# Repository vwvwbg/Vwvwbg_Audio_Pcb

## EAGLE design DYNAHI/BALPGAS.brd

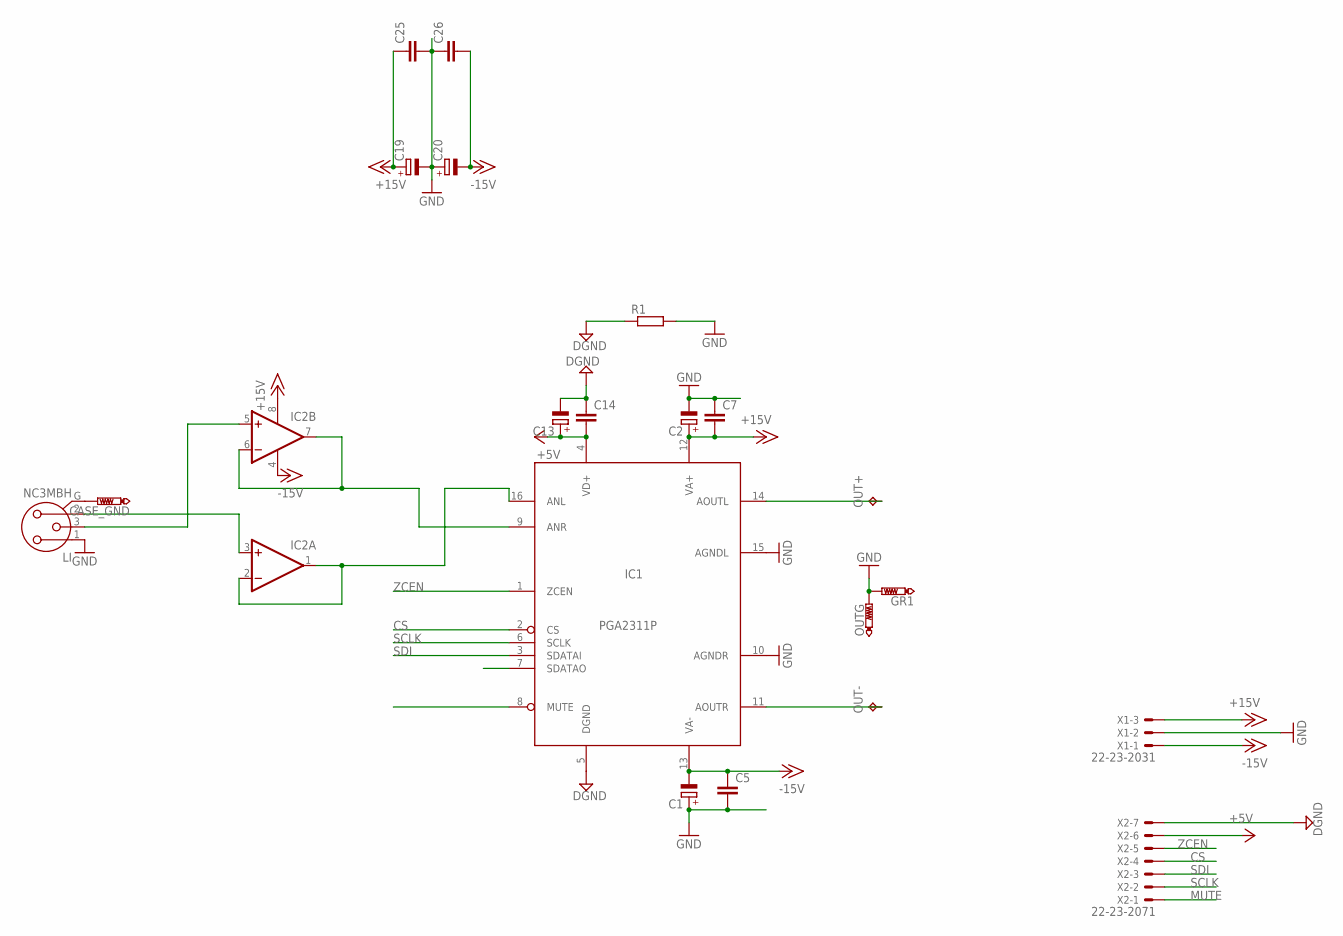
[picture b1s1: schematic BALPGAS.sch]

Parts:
C1, C2, C19, C20: CPOL-EUE5-10.5; E5-10,5
C5, C7, C25, C26: C-EU050-045X075; C050-045X075
C13: CPOL-EUSMCD; SMC_D
C14: C-EUC1206; C1206
CASE_GND: PTR1PAD1-17; P1-17
GR1: PTR1PAD1-17; P1-17
IC1: PGA2311P; DIL16
IC2: 2AMP_P8+4N; DIL08
LI: NC3MBH
OUT+: TPPAD1-20; P1-20
OUT-: TPPAD1-20; P1-20
OUTG: PTR1PAD1-17; P1-17
R1: R-EU_0207/10; 0207/10
X1: 22-23-2031
X2: 22-23-2071

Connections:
+5V: C13.+, C14.2, IC1.4 (VD+), X2.6
+15V: C2.+, C7.2, C19.+, C25.1, IC1.12 (VA+), IC2.8 (V+), X1.3
-15V: C1.-, C5.1, C20.-, C26.2, IC1.13 (VA-), IC2.4 (V-), X1.1
CS: IC1.2 (CS), X2.4
DGND: C13.-, C14.1, IC1.5 (DGND), R1.1, X2.7
GND: C1.+, C2.-, C5.2, C7.1, C19.-, C20.+, C25.2, C26.1, GR1.TP, IC1.10 (AGNDR), IC1.15 (AGNDL), LI.1, OUTG.TP, R1.2, X1.2
MUTE: IC1.8 (MUTE), X2.1
unnamed: IC1.9 (ANR), IC2.6 (-IN), IC2.7 (OUT)
unnamed: IC2.3 (+IN), LI.2
unnamed: CASE_GND.TP, LI.G
unnamed: IC2.5 (+IN), LI.3
unnamed: IC1.16 (ANL), IC2.1 (OUT), IC2.2 (-IN)
unnamed: IC1.11 (AOUTR), OUT-.TP
unnamed: IC1.14 (AOUTL), OUT+.TP
SCLK: IC1.6 (SCLK), X2.2
SDI: IC1.3 (SDATAI), X2.3
ZCEN: IC1.1 (ZCEN), X2.5

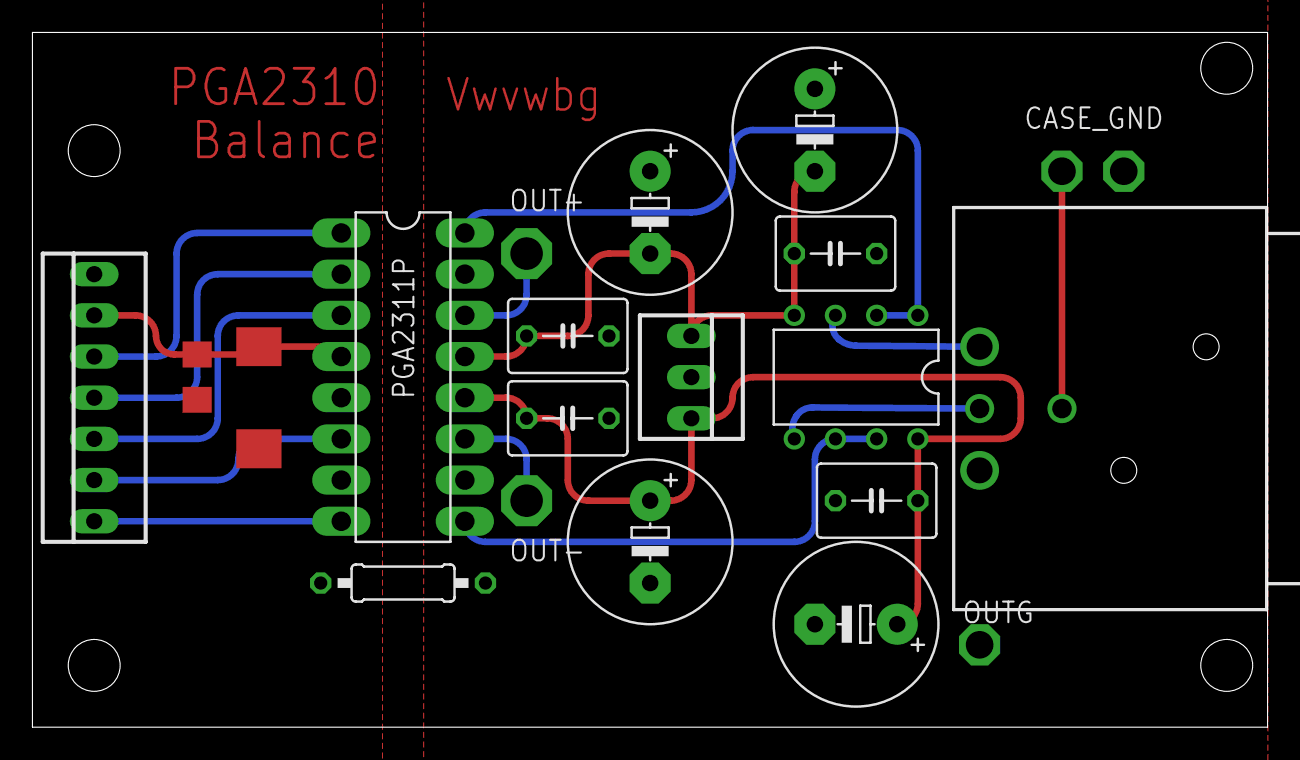
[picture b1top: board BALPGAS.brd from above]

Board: 2 copper layers, 76.2 x 42.9 mm, 21 parts (0 on the bottom side), 17 nets.

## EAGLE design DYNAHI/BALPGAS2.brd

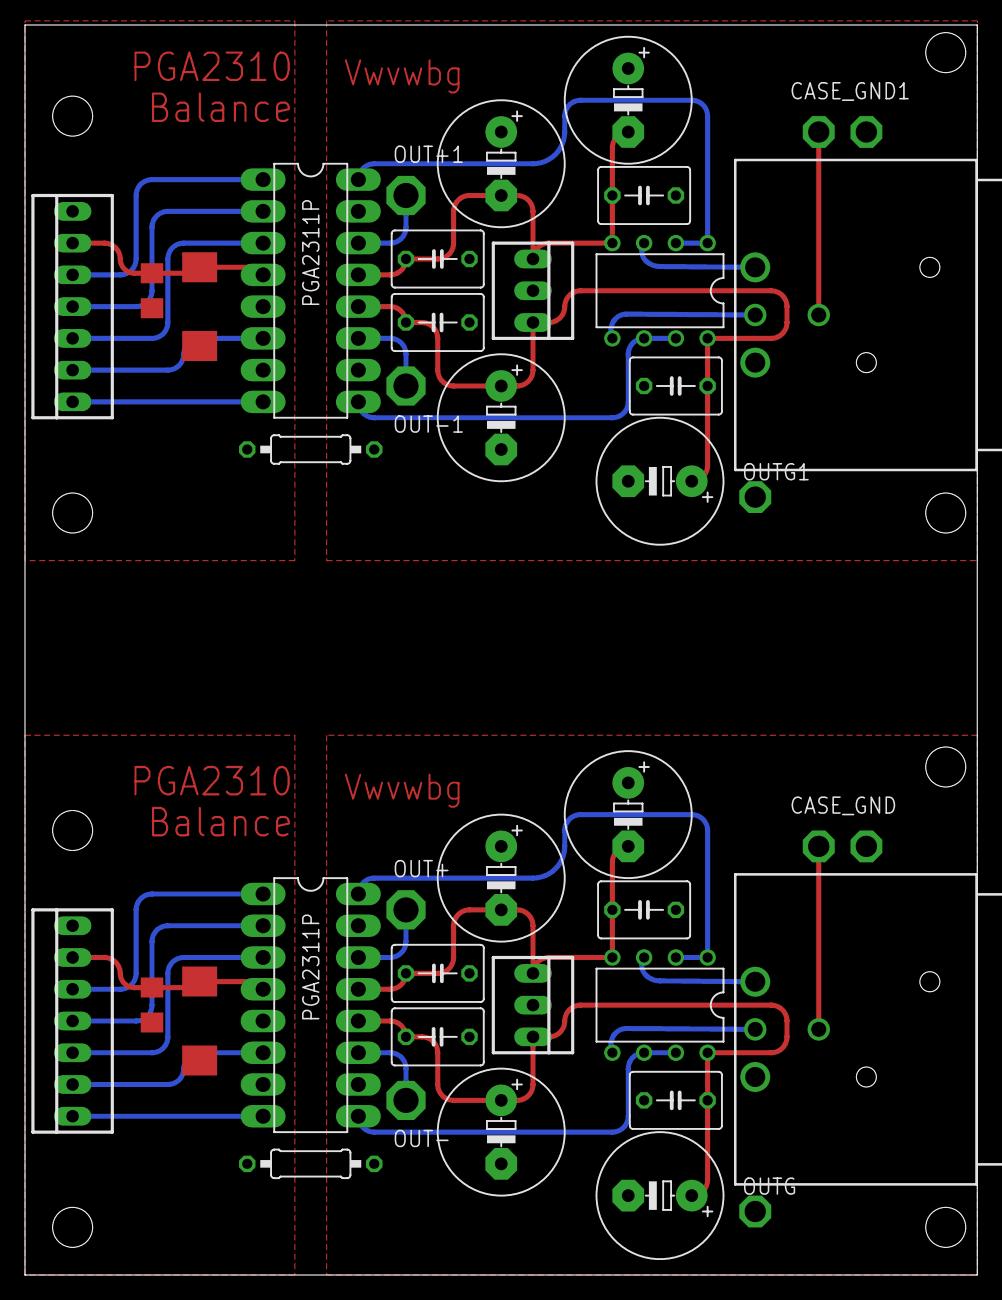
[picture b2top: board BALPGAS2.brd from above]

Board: 2 copper layers, 76.2 x 100.0 mm, 42 parts (0 on the bottom side), 34 nets.

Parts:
C1, C2, C3, C8, C9, C10, C19, C20: E5-10,5
C4, C13: SMC_D
C5, C7, C11, C12, C15, C16, C25, C26: C050-045X075
C6, C14: C1206
CASE_GND, CASE_GND1: PTR1PAD1-17; P1-17
GR1, GR2: PTR1PAD1-17; P1-17
IC1, IC3: PGA2311P; DIL16
IC2, IC4: DIL08
LI, LI1: NC3MBH
OUT+, OUT+1: TPPAD1-20; P1-20
OUT-, OUT-1: TPPAD1-20; P1-20
OUTG, OUTG1: PTR1PAD1-17; P1-17
R1, R2: 0207/10
X1, X3: 22-23-2031
X2, X4: 22-23-2071

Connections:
+5V: C13.+, C14.2, IC1.4, X2.6
+5V1: C4.+, C6.2, IC3.4, X4.6
+15V: C2.+, C7.2, C19.+, C25.1, IC1.12, IC2.8, X1.3
+15V1: C8.+, C9.+, C11.1, C16.2, IC3.12, IC4.8, X3.3
-15V: C1.-, C5.1, C20.-, C26.2, IC1.13, IC2.4, X1.1
-15V1: C3.-, C10.-, C12.2, C15.1, IC3.13, IC4.4, X3.1
CS: IC1.2, X2.4
CS1: IC3.2, X4.4
DGND: C13.-, C14.1, IC1.5, R1.1, X2.7
DGND1: C4.-, C6.1, IC3.5, R2.1, X4.7
GND: C1.+, C2.-, C5.2, C7.1, C19.-, C20.+, C25.2, C26.1, GR1.TP, IC1.10, IC1.15, LI.1, OUTG.TP, R1.2, X1.2
GND1: C3.+, C8.-, C9.-, C10.+, C11.2, C12.1, C15.2, C16.1, GR2.TP, IC3.10, IC3.15, LI1.1, OUTG1.TP, R2.2, X3.2
MUTE: IC1.8, X2.1
MUTE1: IC3.8, X4.1
unnamed: IC1.9, IC2.6, IC2.7
unnamed: IC2.3, LI.2
unnamed: CASE_GND.TP, LI.G
unnamed: IC2.5, LI.3
unnamed: IC3.16, IC4.1, IC4.2
unnamed: IC3.14, OUT+1.TP
unnamed: IC3.11, OUT-1.TP
unnamed: IC1.16, IC2.1, IC2.2
unnamed: IC1.11, OUT-.TP
unnamed: IC1.14, OUT+.TP
unnamed: IC3.9, IC4.6, IC4.7
unnamed: IC4.3, LI1.2
unnamed: IC4.5, LI1.3
unnamed: CASE_GND1.TP, LI1.G
SCLK: IC1.6, X2.2
SCLK1: IC3.6, X4.2
SDI: IC1.3, X2.3
SDI1: IC3.3, X4.3
ZCEN: IC1.1, X2.5
ZCEN1: IC3.1, X4.5

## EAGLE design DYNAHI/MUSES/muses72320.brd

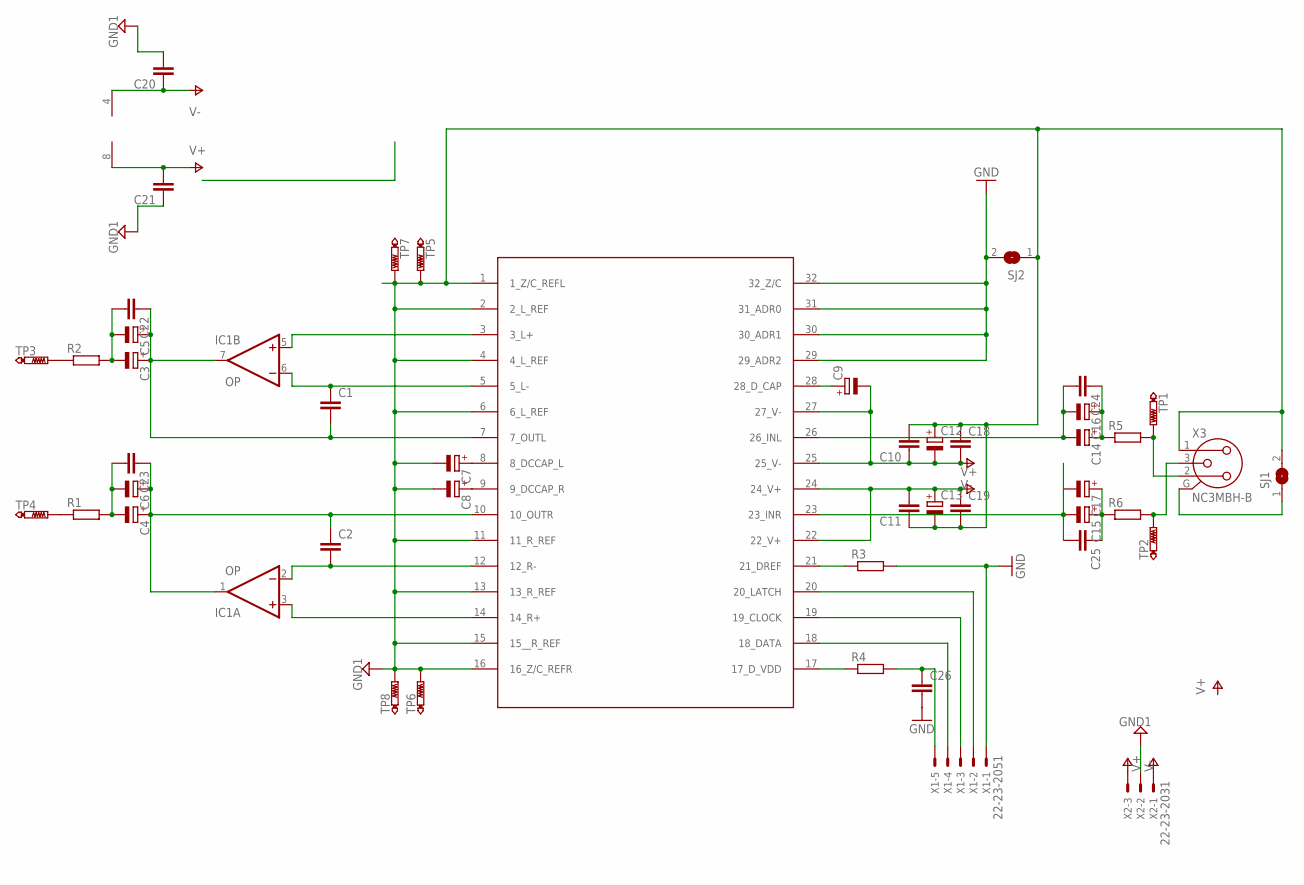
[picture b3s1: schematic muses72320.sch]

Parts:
C1, C2: C-EU075-032X103; C075-032X103
C3, C4, C12, C13, C16, C17: CPOL-EUE5-10.5; E5-10,5
C5, C6, C9, C14, C15: CPOL-EUE3.5-8; E3,5-8
C7, C8: CPOL-EUE5-8.5; E5-8,5
C10, C11, C20, C21, C22, C23, C24, C25: C-EU050-050X075; C050-050X075
C18, C19: C-EU025-030X050; C025-030X050
C26: C-EUC1206; C1206
IC1: OP; DIL08
R1, R2, R5, R6: R-EU_0207/7; 0207/7
R3, R4: R-EU_R1206; R1206
SJ1, SJ2: SJ
TP1, TP2, TP3, TP4, TP5, TP6, TP7, TP8: PTR1PAD1-20; P1-20
U$1: MUSES72320; SSOP28DB
X1: 22-23-2051
X2: 22-23-2031
X3: NC3MBH-B

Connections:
CLOCK: U$1.19 (19_CLOCK), X1.3
DATA: U$1.18 (18_DATA), X1.4
GND: C26.2, R3.2, SJ2.2, U$1.29 (29_ADR2), U$1.30 (30_ADR1), U$1.31 (31_ADR0), U$1.32 (32_Z/C), X1.1
GND1: C7.-, C8.-, C10.2, C11.1, C12.+, C13.-, C18.1, C19.2, C20.2, C21.1, SJ1.2, SJ2.1, TP5.TP, TP6.TP, TP7.TP, TP8.TP, U$1.1 (1_Z/C_REFL), U$1.2 (2_L_REF), U$1.4 (4_L_REF), U$1.6 (6_L_REF), U$1.11 (11_R_REF), U$1.13 (13_R_REF), U$1.15 (15__R_REF), U$1.16 (16_Z/C_REFR), X2.2, X3.1
LATCH: U$1.20 (20_LATCH), X1.2
unnamed: IC1.3 (+IN), U$1.14 (14_R+)
unnamed: C2.2, IC1.2 (-IN), U$1.12 (12_R-)
unnamed: C1.1, IC1.6 (-IN), U$1.5 (5_L-)
unnamed: IC1.5 (+IN), U$1.3 (3_L+)
unnamed: C1.2, C3.+, C5.+, C22.1, IC1.7 (OUT), U$1.7 (7_OUTL)
unnamed: C2.1, C4.+, C6.+, C23.1, IC1.1 (OUT), U$1.10 (10_OUTR)
unnamed: C3.-, C5.-, C22.2, R2.2
unnamed: C4.-, C6.-, C23.2, R1.2
unnamed: C7.+, U$1.8 (8_DCCAP_L)
unnamed: C8.+, U$1.9 (9_DCCAP_R)
unnamed: SJ1.1, X3.G
unnamed: R5.2, TP1.TP, X3.2
unnamed: R6.2, TP2.TP, X3.3
unnamed: R3.1, U$1.21 (21_DREF)
unnamed: R4.1, U$1.17 (17_D_VDD)
unnamed: C9.+, U$1.28 (28_D_CAP)
unnamed: R2.1, TP3.TP
unnamed: R1.1, TP4.TP
unnamed: C26.1, R4.2, X1.5
unnamed: C15.-, C17.-, C25.2, U$1.23 (23_INR)
unnamed: C14.-, C16.-, C24.2, U$1.26 (26_INL)
unnamed: C14.+, C16.+, C24.1, R5.1
unnamed: C15.+, C17.+, C25.1, R6.1
V+: C11.2, C13.+, C19.1, C21.2, IC1.8 (V+), U$1.22 (22_V+), U$1.24 (24_V+), X2.1
V-: C9.-, C10.1, C12.-, C18.2, C20.1, IC1.4 (V-), U$1.25 (25_V-), U$1.27 (27_V-), X2.3

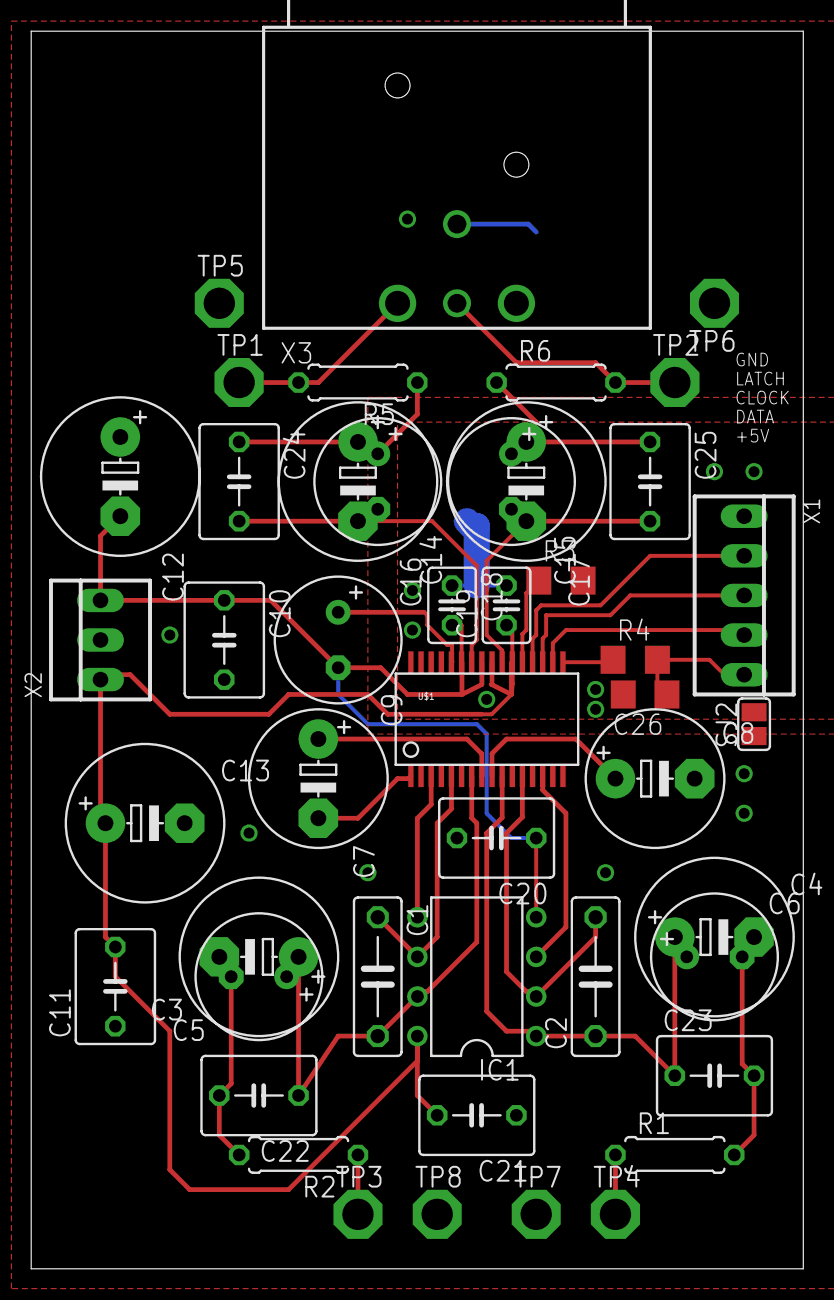
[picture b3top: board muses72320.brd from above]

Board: 2 copper layers, 49.5 x 79.4 mm, 47 parts (1 on the bottom side), 30 nets.

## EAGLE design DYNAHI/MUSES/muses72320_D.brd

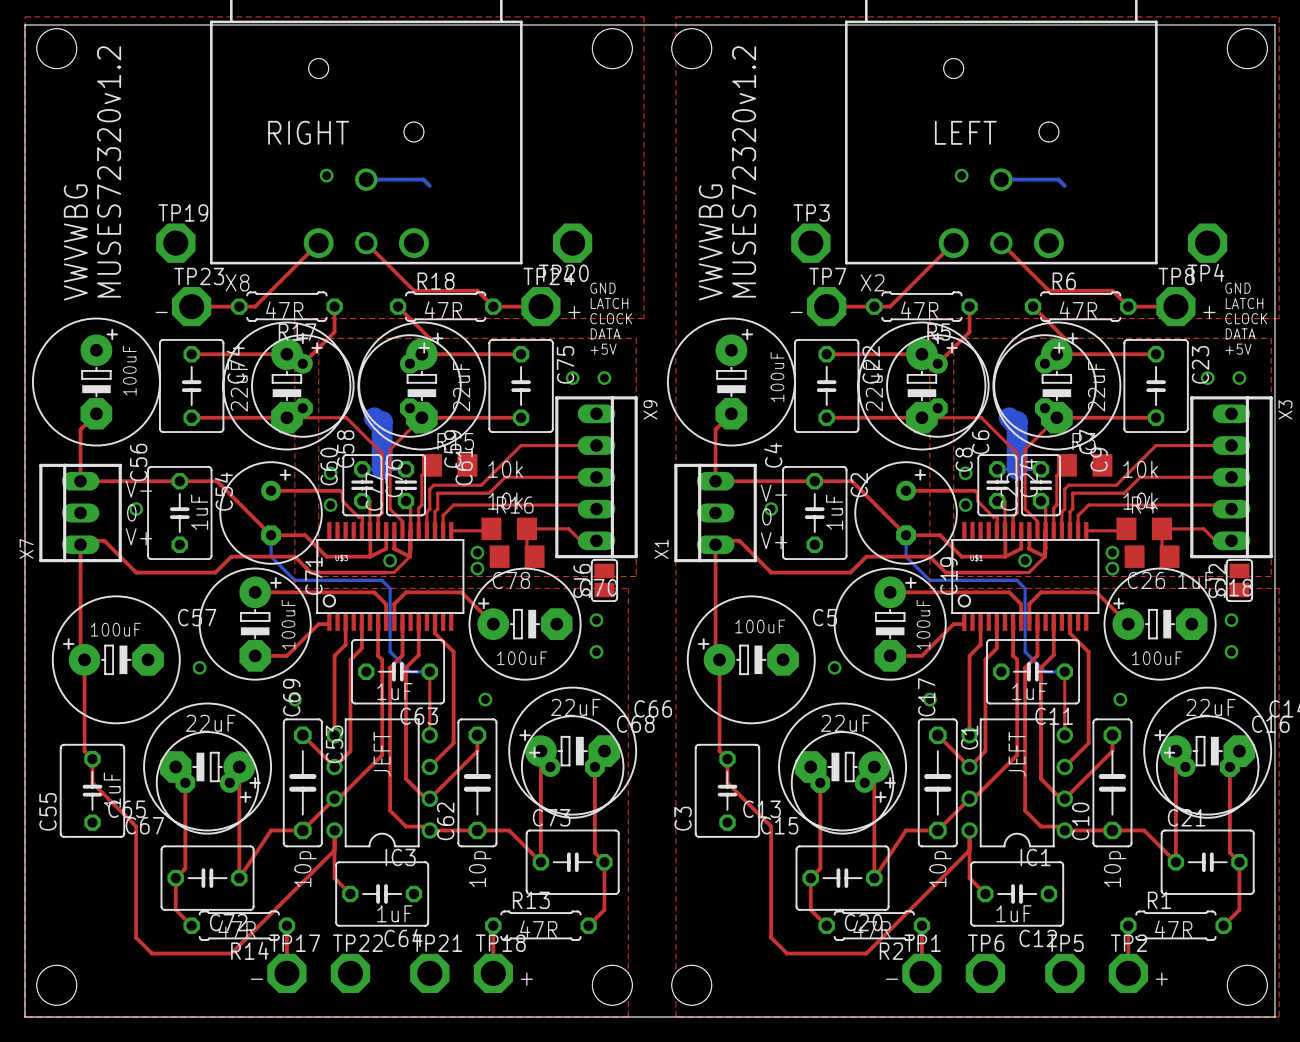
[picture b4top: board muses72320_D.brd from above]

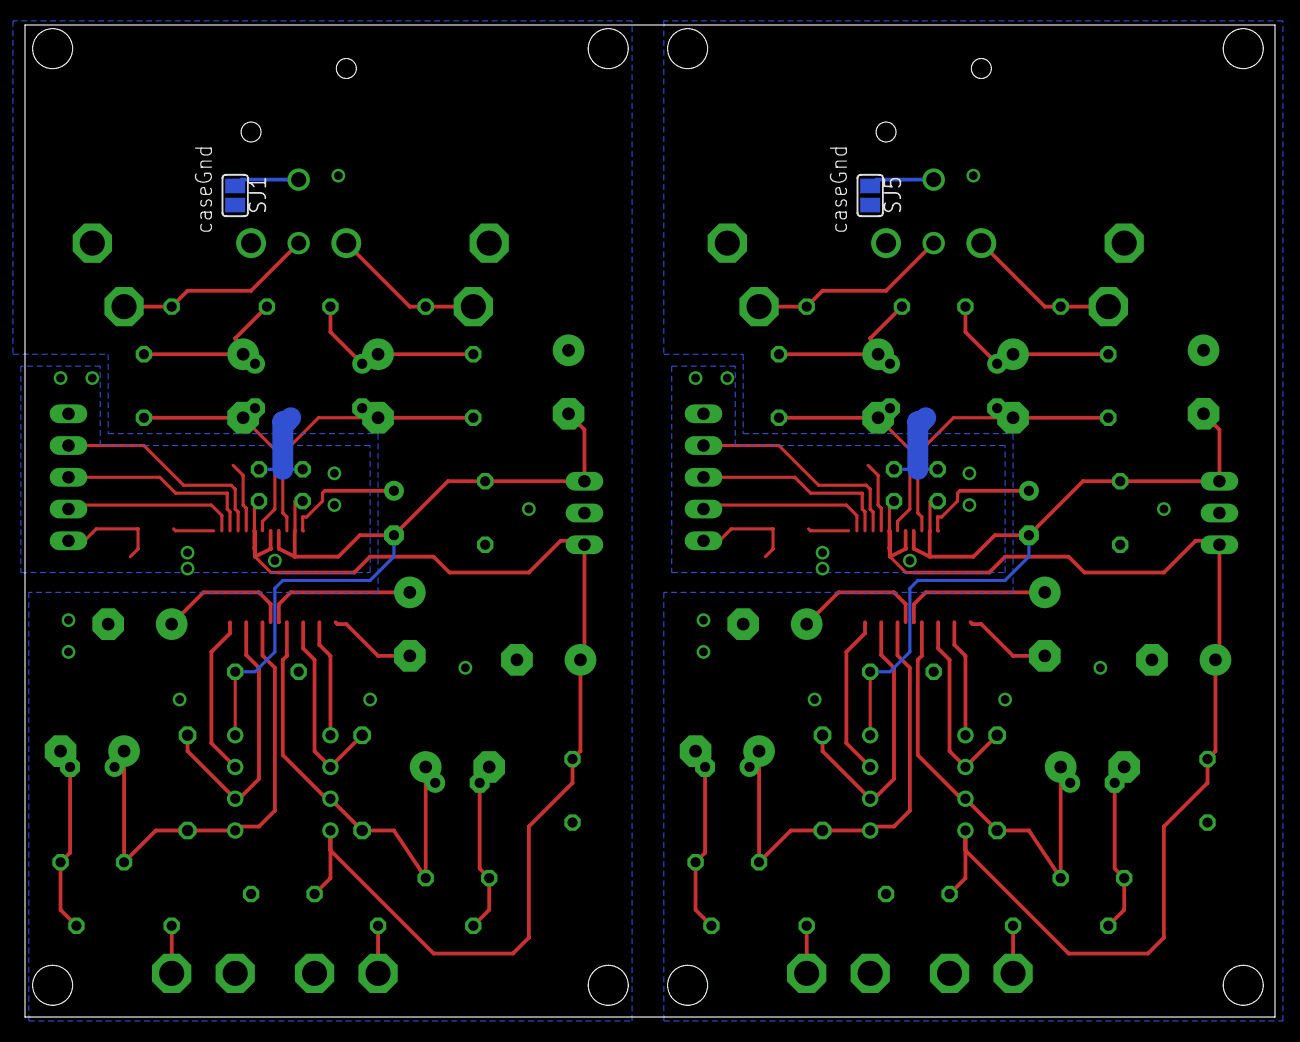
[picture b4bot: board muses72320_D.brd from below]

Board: 2 copper layers, 100.0 x 79.4 mm, 94 parts (2 on the bottom side), 60 nets.

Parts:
C1, C10, C53, C62: C075-032X103
C2, C3, C11, C12, C20, C21, C22, C23, C54, C55, C63, C64, C72, C73, C74, C75: C050-050X075
C4, C5, C8, C9, C13, C14, C56, C57, C60, C61, C65, C66: E5-10,5
C6, C7, C15, C16, C19, C58, C59, C67, C68, C71: E3,5-8
C17, C18, C69, C70: E5-8,5
C24, C25, C76, C77: C025-030X050
C26, C78: C1206
IC1, IC3: OP; DIL08
R1, R2, R5, R6, R13, R14, R17, R18: 0207/7
R3, R4, R15, R16: R1206
SJ1, SJ2, SJ5, SJ6: SJ
TP1, TP2, TP3, TP4, TP5, TP6, TP7, TP8, TP17, TP18, TP19, TP20, TP21, TP22, TP23, TP24: PTR1PAD1-20; P1-20
U$1, U$3: MUSES72320; SSOP28DB
X1, X7: 22-23-2031
X2, X8: NC3MBH-B
X3, X9: 22-23-2051

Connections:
CLOCK1: U$1.19, X3.3
CLOCK2: U$3.19, X9.3
DATA1: U$1.18, X3.4
DATA2: U$3.18, X9.4
GND1: C26.2, R3.2, SJ2.2, U$1.29, U$1.30, U$1.31, U$1.32, X3.1
GND2: C2.2, C3.1, C4.+, C5.-, C11.2, C12.1, C17.-, C18.-, C24.1, C25.2, SJ1.2, SJ2.1, TP3.TP, TP4.TP, TP5.TP, TP6.TP, U$1.1, U$1.2, U$1.4, U$1.6, U$1.11, U$1.13, U$1.15, U$1.16, X1.2, X2.1
GND4: C78.2, R15.2, SJ6.2, U$3.29, U$3.30, U$3.31, U$3.32, X9.1
GND5: C54.2, C55.1, C56.+, C57.-, C63.2, C64.1, C69.-, C70.-, C76.1, C77.2, SJ5.2, SJ6.1, TP19.TP, TP20.TP, TP21.TP, TP22.TP, U$3.1, U$3.2, U$3.4, U$3.6, U$3.11, U$3.13, U$3.15, U$3.16, X7.2, X8.1
LATCH1: U$1.20, X3.2
LATCH2: U$3.20, X9.2
unnamed: IC1.3, U$1.14
unnamed: C10.2, IC1.2, U$1.12
unnamed: C1.1, IC1.6, U$1.5
unnamed: IC1.5, U$1.3
unnamed: C1.2, C13.+, C15.+, C20.1, IC1.7, U$1.7
unnamed: C10.1, C14.+, C16.+, C21.1, IC1.1, U$1.10
unnamed: C13.-, C15.-, C20.2, R2.2
unnamed: C14.-, C16.-, C21.2, R1.2
unnamed: C17.+, U$1.8
unnamed: C18.+, U$1.9
unnamed: R3.1, U$1.21
unnamed: R4.1, U$1.17
unnamed: C19.+, U$1.28
unnamed: C7.-, C9.-, C23.2, U$1.23
unnamed: C6.-, C8.-, C22.2, U$1.26
unnamed: C6.+, C8.+, C22.1, R5.1
unnamed: C7.+, C9.+, C23.1, R6.1
unnamed: C26.1, R4.2, X3.5
unnamed: R2.1, TP1.TP
unnamed: R1.1, TP2.TP
unnamed: SJ1.1, X2.G
unnamed: R5.2, TP7.TP, X2.2
unnamed: R6.2, TP8.TP, X2.3
unnamed: IC3.3, U$3.14
unnamed: C62.2, IC3.2, U$3.12
unnamed: C53.1, IC3.6, U$3.5
unnamed: IC3.5, U$3.3
unnamed: C53.2, C65.+, C67.+, C72.1, IC3.7, U$3.7
unnamed: C62.1, C66.+, C68.+, C73.1, IC3.1, U$3.10
unnamed: C65.-, C67.-, C72.2, R14.2
unnamed: C66.-, C68.-, C73.2, R13.2
unnamed: C69.+, U$3.8
unnamed: C70.+, U$3.9
unnamed: R15.1, U$3.21
unnamed: R16.1, U$3.17
unnamed: C71.+, U$3.28
unnamed: C59.-, C61.-, C75.2, U$3.23
unnamed: C58.-, C60.-, C74.2, U$3.26
unnamed: C58.+, C60.+, C74.1, R17.1
unnamed: C59.+, C61.+, C75.1, R18.1
unnamed: C78.1, R16.2, X9.5
unnamed: R14.1, TP17.TP
unnamed: R13.1, TP18.TP
unnamed: SJ5.1, X8.G
unnamed: R17.2, TP23.TP, X8.2
unnamed: R18.2, TP24.TP, X8.3
V+1: C3.2, C5.+, C12.2, C25.1, IC1.8, U$1.22, U$1.24, X1.1
V+2: C55.2, C57.+, C64.2, C77.1, IC3.8, U$3.22, U$3.24, X7.1
V-1: C2.1, C4.-, C11.1, C19.-, C24.2, IC1.4, U$1.25, U$1.27, X1.3
V-2: C54.1, C56.-, C63.1, C71.-, C76.2, IC3.4, U$3.25, U$3.27, X7.3

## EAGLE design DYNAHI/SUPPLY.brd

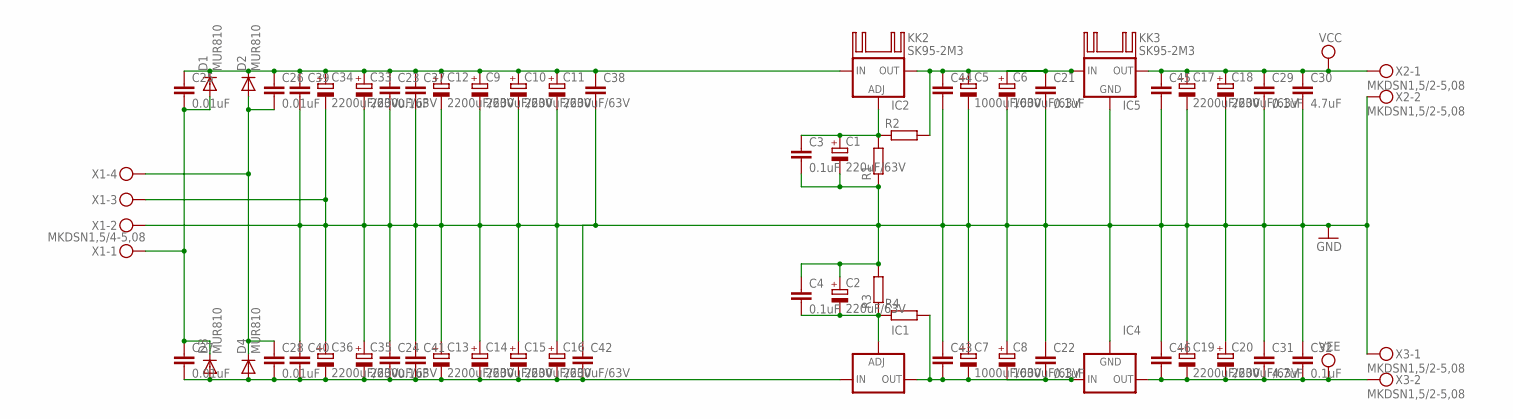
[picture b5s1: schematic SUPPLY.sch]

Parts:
C1, C2: 220uF/63V; E5-10,5
C3, C4, C21, C22, C23, C24: 0.1uF; C050-035X075
C5, C6, C7, C8: 1000uF/63V; E7,5-16
C9, C10, C11, C12, C13, C14, C15, C16, C17, C18, C19, C20, C33, C34, C35, C36: 2200uF/63V; E7,5-18
C25, C26, C27, C28: 0.01uF; C050-035X075
C29, C32: 0.1uF; C102-054X133
C30, C31: 4.7uF; C102-054X133
C37, C38, C39, C40, C41, C42, C43, C44, C45, C46: C-EUC1210; C1210
D1, D2, D3, D4: MUR810; TO220ACS
IC1: LM337TS; 337TS
IC2: LM317TS; 317TS
IC4: 79XXS
IC5: 78XXS
KK2, KK3: SK95-2M3
R1, R2, R3, R4: R-EU_0207/10; 0207/10
X1: MKDSN1,5/4-5,08
X2, X3: MKDSN1,5/2-5,08

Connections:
GND: C1.-, C2.+, C3.2, C4.1, C5.-, C6.-, C7.+, C8.+, C9.-, C10.-, C11.-, C12.-, C13.+, C14.+, C15.+, C16.+, C17.-, C18.-, C19.+, C20.+, C21.2, C22.1, C23.2, C24.1, C29.2, C30.2, C31.1, C32.1, C33.-, C34.-, C35.+, C36.+, C37.2, C38.2, C39.2, C40.1, C41.1, C42.1, C43.1, C44.2, C45.2, C46.1, IC4.GND, IC5.GND, R1.1, R3.2, X1.2, X1.3, X2.2, X3.1
unnamed: C2.-, C4.2, IC1.1 (ADJ), R3.1, R4.1
unnamed: C1.+, C3.1, IC2.1 (ADJ), R1.2, R2.1
unnamed: C25.2, C27.1, D1.A, D3.C, X1.1
unnamed: C26.2, C28.1, D2.A, D4.C, X1.4
VCC: C17.+, C18.+, C29.1, C30.1, C45.1, IC5.OUT, X2.1
VCCIN: C9.+, C10.+, C11.+, C12.+, C23.1, C25.1, C26.1, C33.+, C34.+, C37.1, C38.1, C39.1, D1.C, D2.C, IC2.3 (IN)
VCCP: C5.+, C6.+, C21.1, C44.1, IC2.2 (OUT), IC5.IN, R2.2
VEE: C19.-, C20.-, C31.2, C32.2, C46.2, IC4.OUT, X3.2
VEEIN: C13.-, C14.-, C15.-, C16.-, C24.2, C27.2, C28.2, C35.-, C36.-, C40.2, C41.2, C42.2, D3.A, D4.A, IC1.2 (IN)
VEEP: C7.-, C8.-, C22.2, C43.2, IC1.3 (OUT), IC4.IN, R4.2

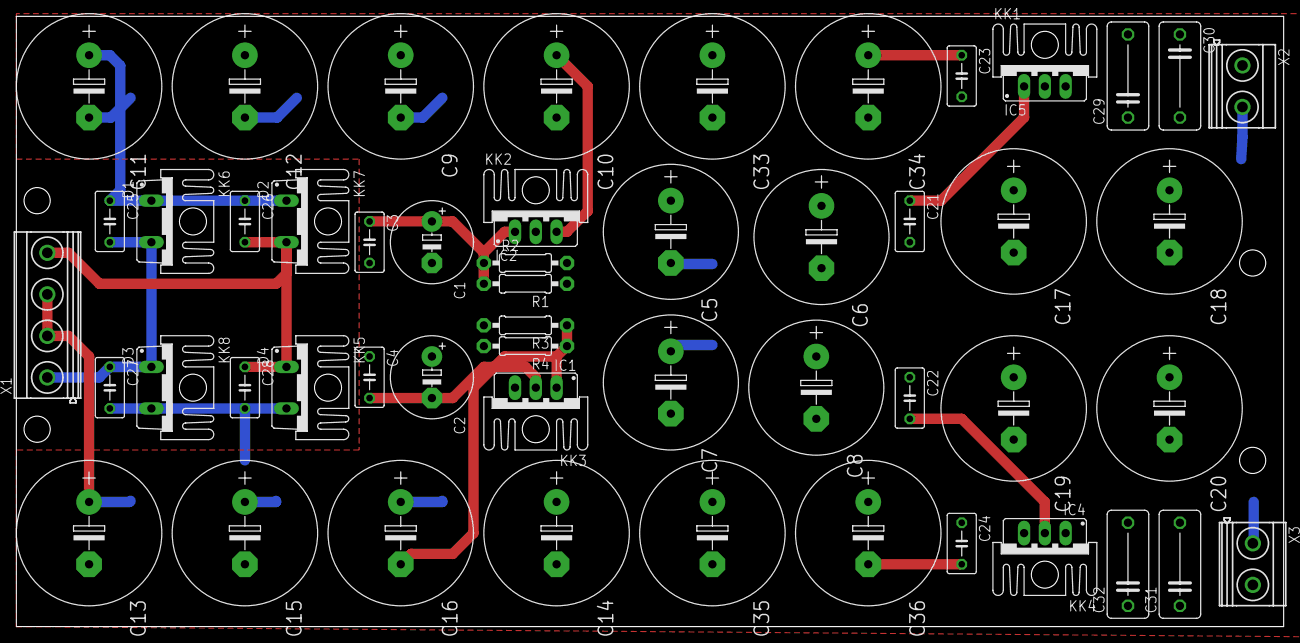
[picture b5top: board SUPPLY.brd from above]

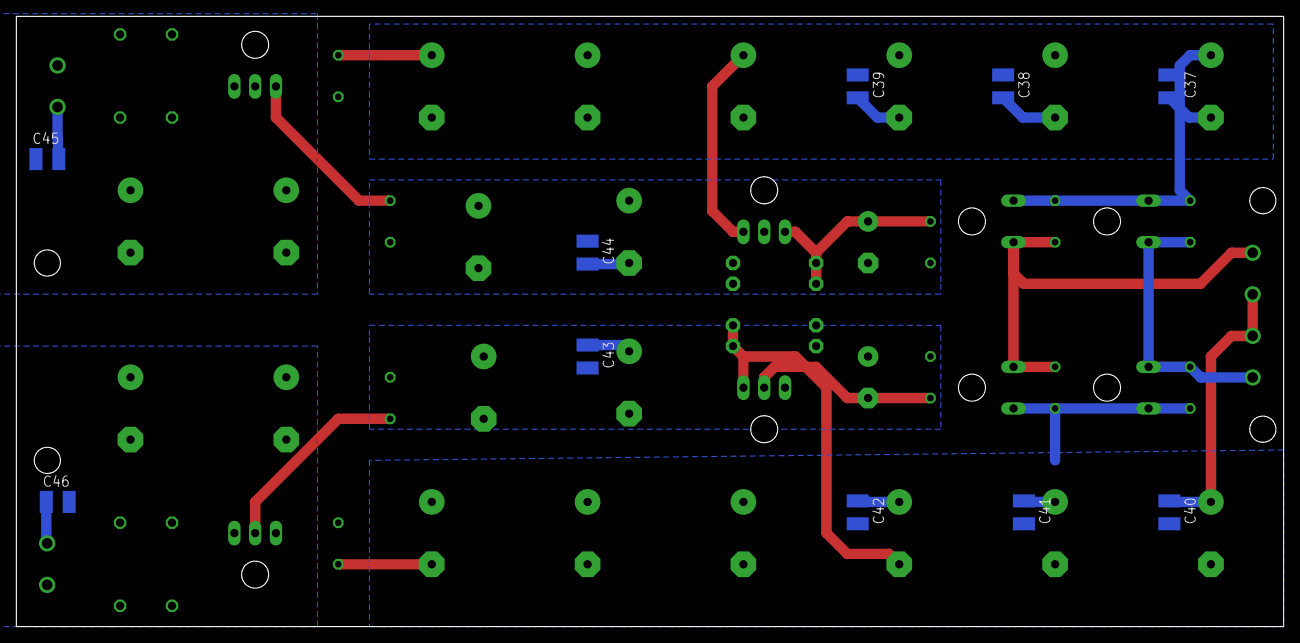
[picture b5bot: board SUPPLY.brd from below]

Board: 2 copper layers, 154.9 x 74.6 mm, 69 parts (10 on the bottom side), 11 nets.

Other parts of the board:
KK1, KK4, KK5, KK6, KK7, KK8: SK95-2M3

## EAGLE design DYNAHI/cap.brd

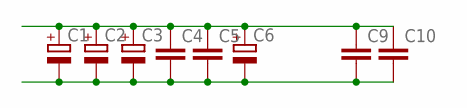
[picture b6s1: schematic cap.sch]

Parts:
C1, C2, C3, C6: CPOL-EUE7.5-18; E7,5-18
C4, C5, C9, C10: C-EU075-052X106; C075-052X106

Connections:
V+: C1.+, C2.+, C3.+, C4.1, C5.1, C6.+, C9.1, C10.1
V-: C1.-, C2.-, C3.-, C4.2, C5.2, C6.-, C9.2, C10.2

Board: 2 copper layers, 8 parts (0 on the bottom side), 2 nets, no tracks yet.

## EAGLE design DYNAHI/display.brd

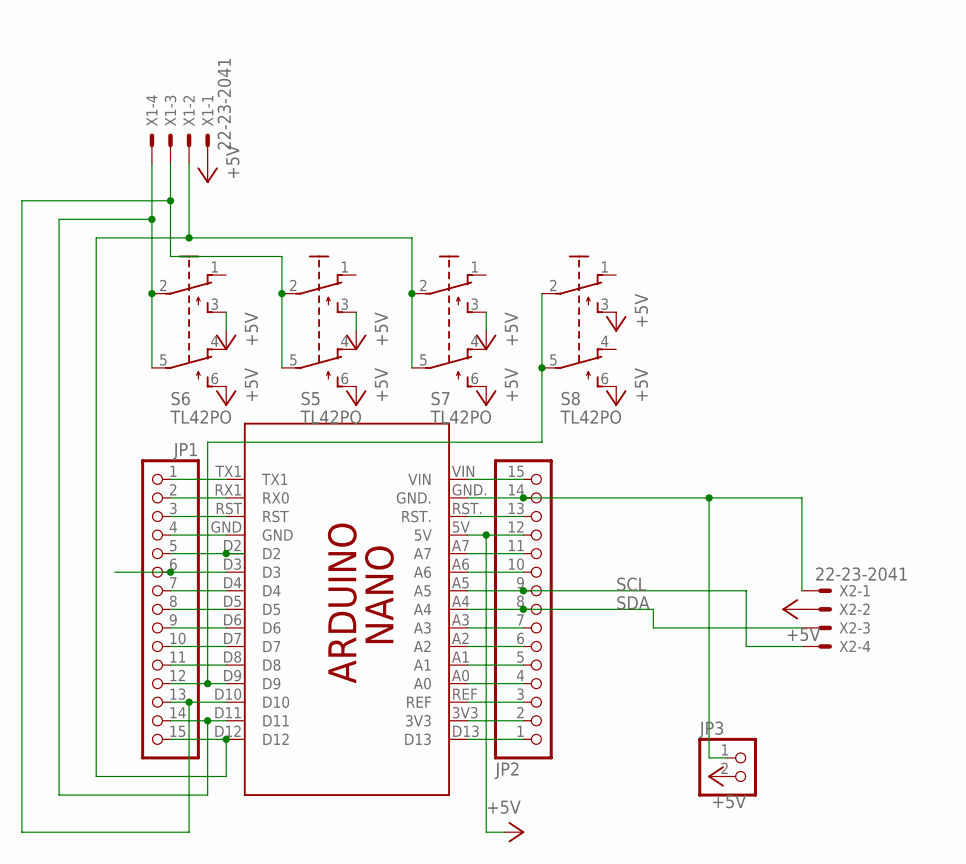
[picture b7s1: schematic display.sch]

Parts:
JP1, JP2: PINHD-1X15; 1X15
JP3: PINHD-1X2; 1X02
PCB1: ARDUINO_NANO
S5, S6, S7, S8: TL42PO; TL4XPO
X1, X2: 22-23-2041

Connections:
+5V: JP2.12, JP3.2, PCB1.5V, S5.3 (S), S5.6 (S1), S6.3 (S), S6.6 (S1), S7.3 (S), S7.6 (S1), S8.3 (S), S8.6 (S1), X1.1, X2.2
GND: JP2.14, JP3.1, PCB1.GND., X2.1
unnamed: JP1.13, PCB1.D10, S5.2, S5.5 (P1), X1.3
unnamed: JP1.15, PCB1.D12, S7.2, S7.5 (P1), X1.2
unnamed: JP1.1, PCB1.TX1
unnamed: JP1.2, PCB1.RX1 (RX0)
unnamed: JP1.3, PCB1.RST
unnamed: JP1.4, PCB1.GND
unnamed: JP1.5, PCB1.D2
unnamed: JP1.6, PCB1.D3
unnamed: JP1.7, PCB1.D4
unnamed: JP1.8, PCB1.D5
unnamed: JP1.9, PCB1.D6
unnamed: JP1.10, PCB1.D7
unnamed: JP1.11, PCB1.D8
unnamed: JP1.12, PCB1.D9, S8.2, S8.5 (P1)
unnamed: JP1.14, PCB1.D11, S6.2, S6.5 (P1), X1.4
unnamed: JP2.15, PCB1.VIN
unnamed: JP2.13, PCB1.RST.
unnamed: JP2.11, PCB1.A7
unnamed: JP2.10, PCB1.A6
unnamed: JP2.7, PCB1.A3
unnamed: JP2.6, PCB1.A2
unnamed: JP2.5, PCB1.A1
unnamed: JP2.4, PCB1.A0
unnamed: JP2.2, PCB1.3V3
unnamed: JP2.3, PCB1.REF
unnamed: JP2.1, PCB1.D13
SCL: JP2.9, PCB1.A5, X2.4
SDA: JP2.8, PCB1.A4, X2.3

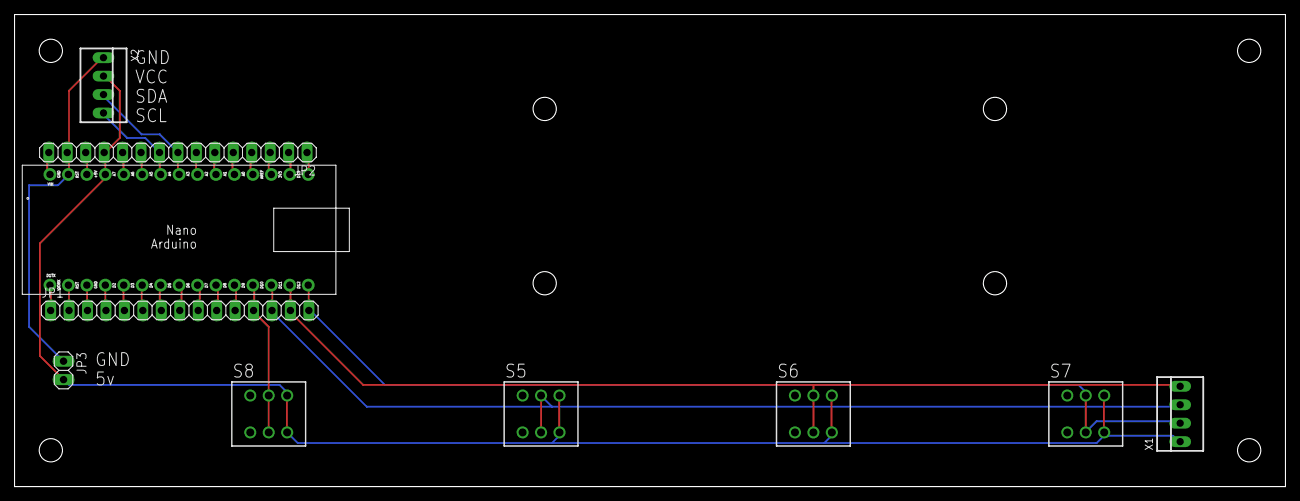
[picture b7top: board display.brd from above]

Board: 2 copper layers, 175.0 x 65.0 mm, 10 parts (0 on the bottom side), 30 nets.

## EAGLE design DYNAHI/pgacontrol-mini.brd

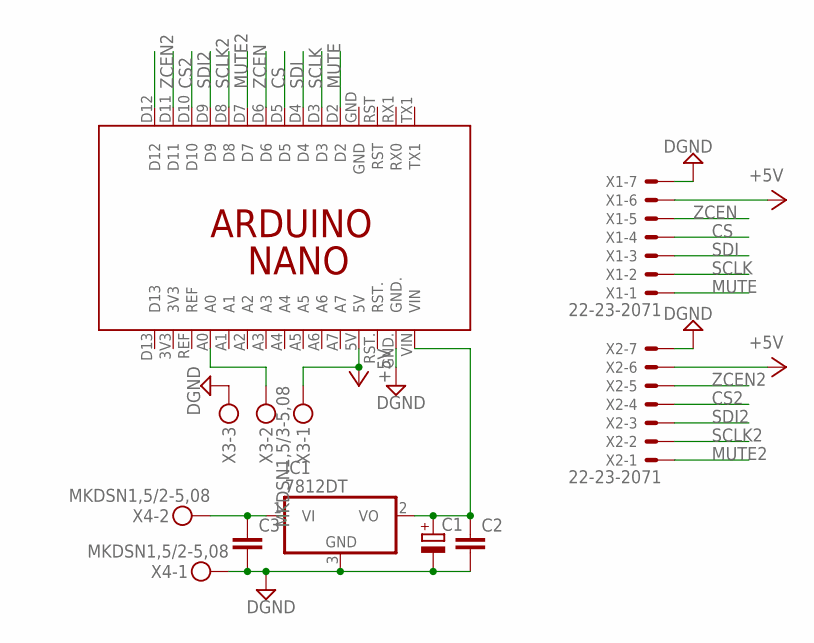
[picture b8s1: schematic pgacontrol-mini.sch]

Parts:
C1: CPOL-EUSMCD; SMC_D
C2, C3: C-EUC1206; C1206
IC1: 7812DT; TO252
PCB1: ARDUINO_NANO
X1, X2: 22-23-2071
X3: MKDSN1,5/3-5,08
X4: MKDSN1,5/2-5,08

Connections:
+5V: PCB1.5V, X1.6, X2.6, X3.1
CS: PCB1.D5, X1.4
CS2: PCB1.D10, X2.4
DGND: C1.-, C2.2, C3.2, IC1.3 (GND), PCB1.GND., X1.7, X2.7, X3.3, X4.1
MUTE: PCB1.D2, X1.1
MUTE2: PCB1.D7, X2.1
unnamed: PCB1.A0, X3.2
SCLK: PCB1.D3, X1.2
SCLK2: PCB1.D8, X2.2
SDI: PCB1.D4, X1.3
SDI2: PCB1.D9, X2.3
VI: C3.1, IC1.1 (VI), X4.2
VO: C1.+, C2.1, IC1.2 (VO), PCB1.VIN
ZCEN: PCB1.D6, X1.5
ZCEN2: PCB1.D11, X2.5

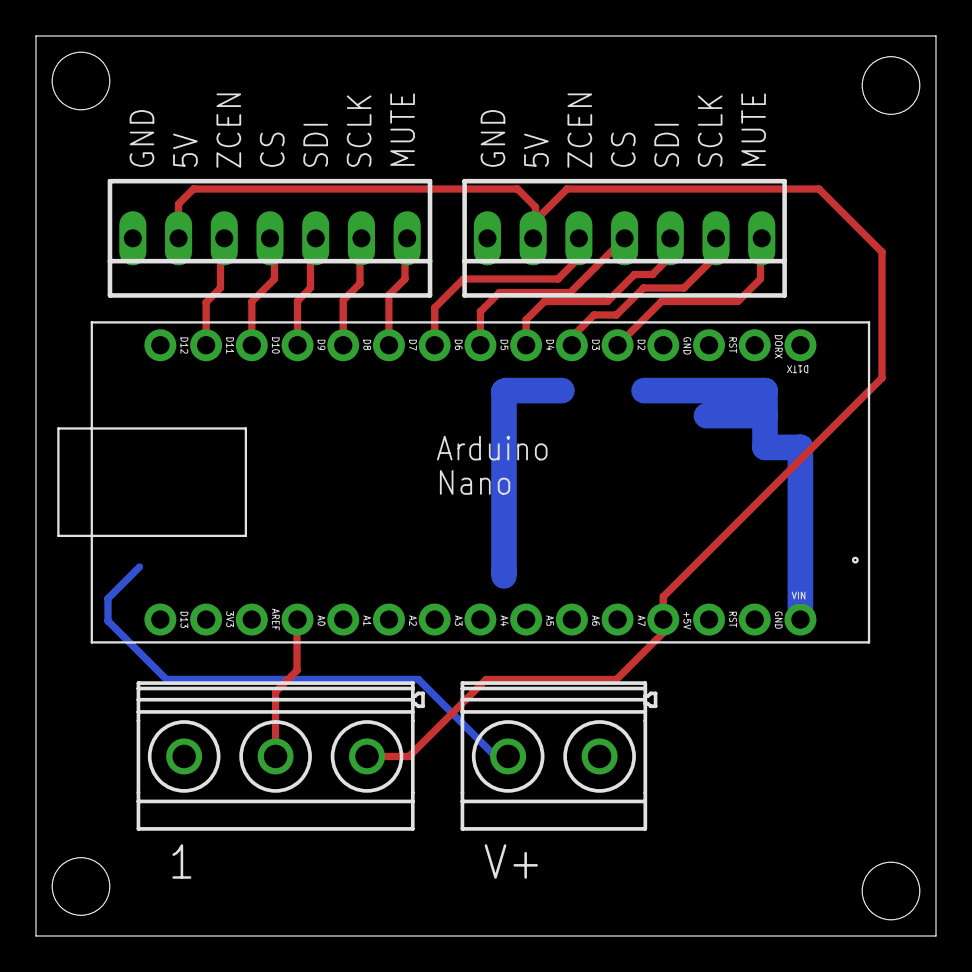
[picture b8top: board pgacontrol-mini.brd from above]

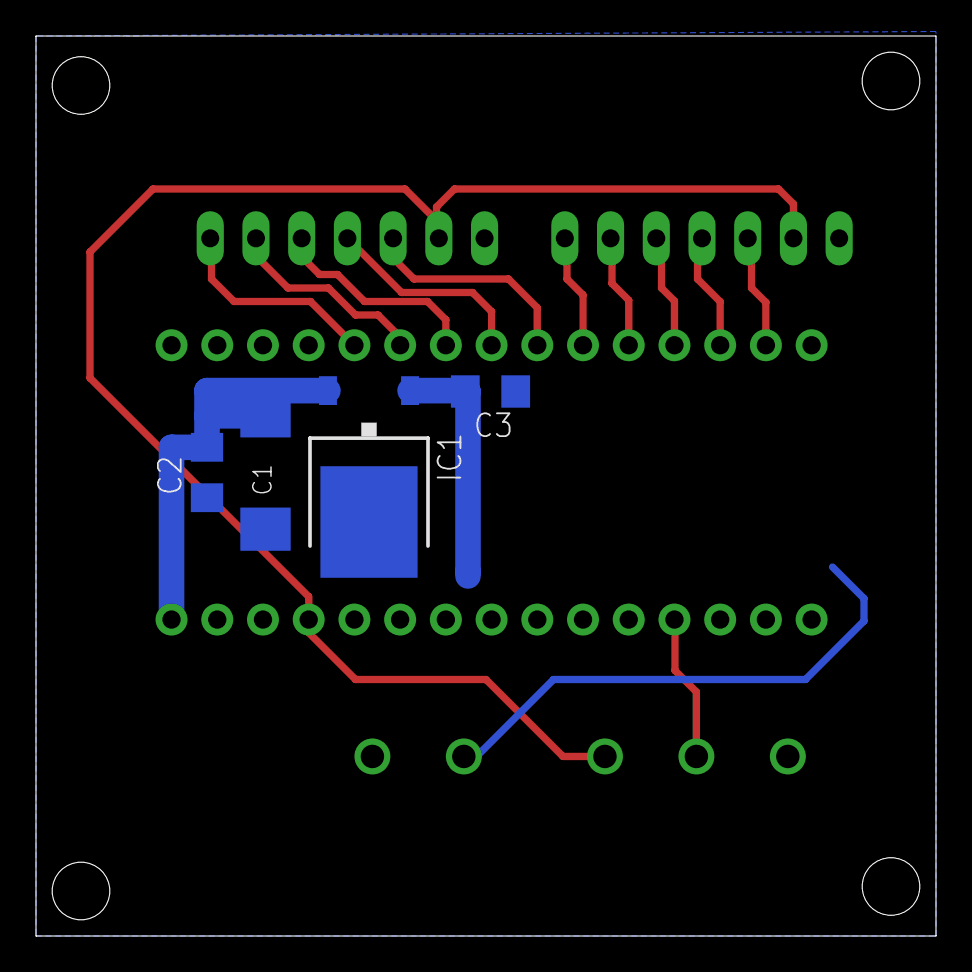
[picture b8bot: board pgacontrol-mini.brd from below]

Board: 2 copper layers, 50.0 x 50.0 mm, 9 parts (4 on the bottom side), 15 nets.
